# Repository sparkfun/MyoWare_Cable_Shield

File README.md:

MyoWare™ Cable Shield
========================================

[*MyoWare™ Cable Shield (DEV-13687)*](https://www.sparkfun.com/products/13687)

The MyoWare™ Cable Shield is designed to pair with the MyoWare™ Muscle Sensor. This shield provides a jack for a [biomedical sensor pad cable](https://www.sparkfun.com/products/12970).

Repository Contents
-------------------

* **/Hardware** - Eagle design files (.brd, .sch)
* **/Production** - Production panel files (.brd)

Documentation
--------------
* **[Hookup Guide](https://learn.sparkfun.com/tutorials/myoware-muscle-sensor-kit)** - Basic hookup guide for the MyoWare™ Cable Shield.

Product Versions
----------------
* [v1.0](https://www.sparkfun.com/products/13687)- MyoWare™ Cable Shield

License Information
-------------------

This product is _**open source**_!

Please review the LICENSE.md file for license information.

If you have any questions or concerns on licensing, please contact techsupport@sparkfun.com.

Distributed as-is; no warranty is given.

- Your friends at SparkFun.

Designed by Brian E. Kaminski of Advancer Technologies

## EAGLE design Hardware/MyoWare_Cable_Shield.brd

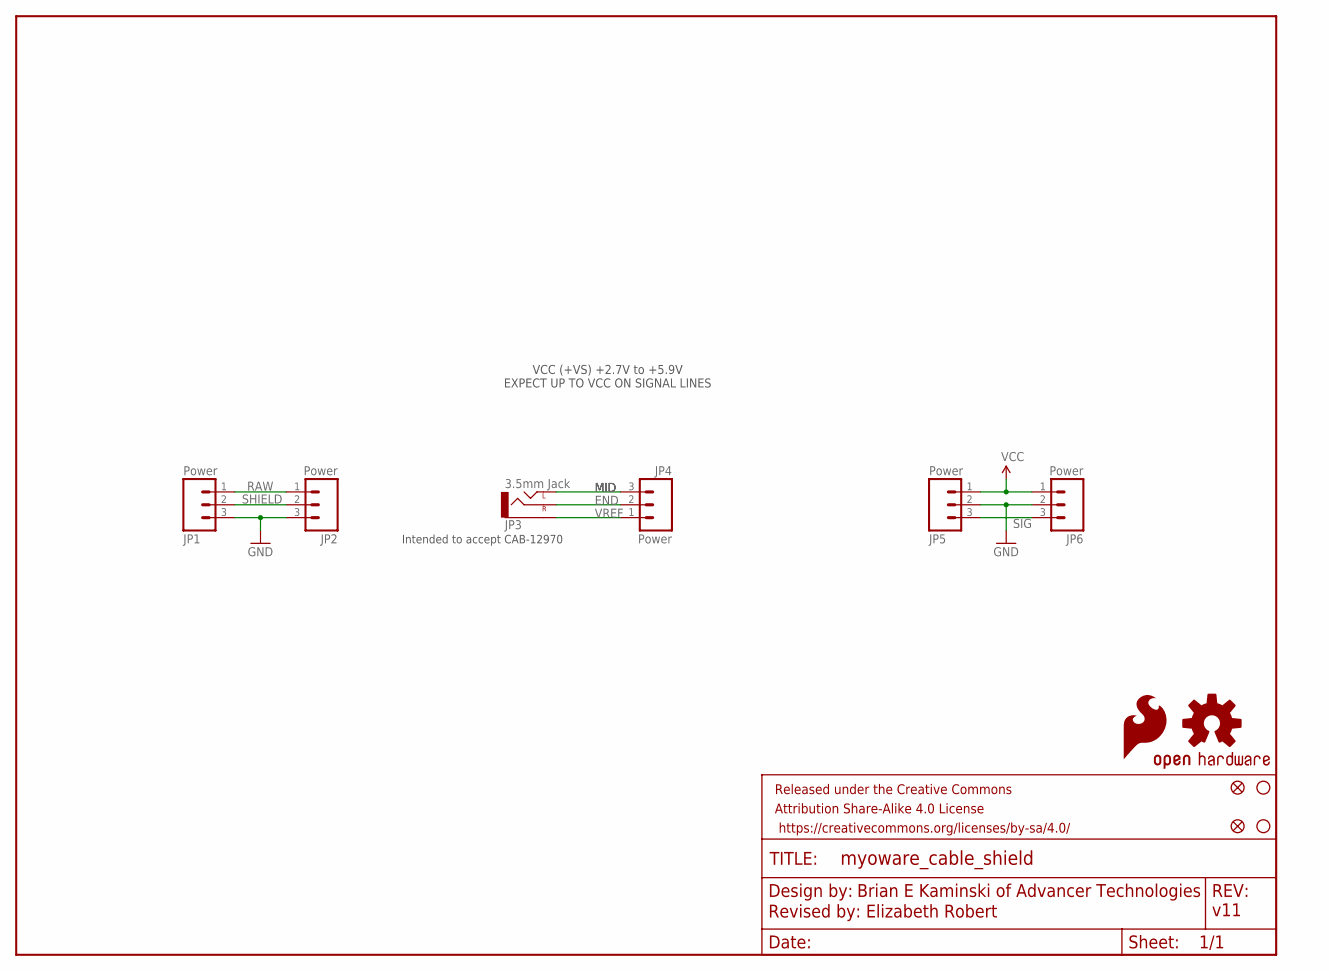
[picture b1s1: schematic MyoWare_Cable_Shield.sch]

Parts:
FID1, FID2: FIDUCIAL1X2; FIDUCIAL-1X2
FRAME1: FRAME-LETTER; CREATIVE_COMMONS
JP1, JP2, JP4, JP5, JP6: Power; 1X03_NO_SILK
JP3: 3.5mm Jack; AUDIO-JACK-3.5MM-SMD
LOGO1: SFE_LOGO_FLAME.2_INCH; SFE_LOGO_FLAME_.2
LOGO2: OSHW-LOGOM; OSHW-LOGO-M
STANDOFF1, STANDOFF2: STAND-OFF

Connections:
END: JP3.RING (RIGHT), JP4.2
GND: JP1.3, JP2.3, JP5.2, JP6.2
MID: JP3.TIP (LEFT), JP4.3
RAW: JP1.1, JP2.1
SHIELD: JP1.2, JP2.2
SIG: JP5.3, JP6.3
VCC: JP5.1, JP6.1
VREF: JP3.SLEEVE, JP4.1

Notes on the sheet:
Brian E Kaminski of Advancer Technologies
Revised by: Elizabeth Robert
v11
VCC (+VS) +2.7V to +5.9V EXPECT UP TO VCC ON SIGNAL LINES
Intended to accept CAB-12970

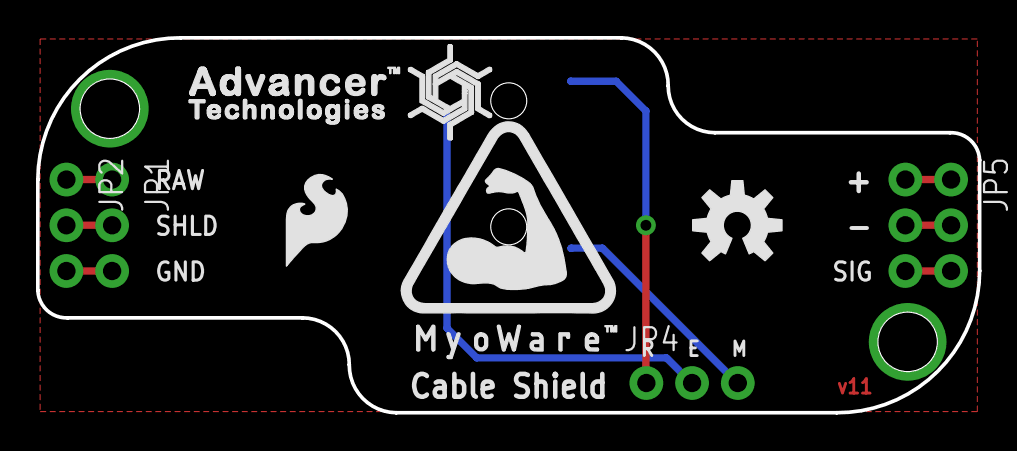
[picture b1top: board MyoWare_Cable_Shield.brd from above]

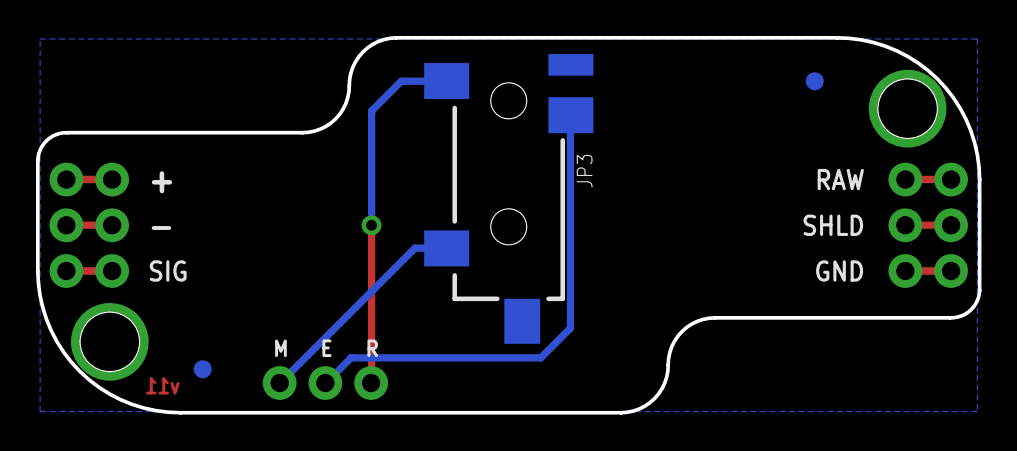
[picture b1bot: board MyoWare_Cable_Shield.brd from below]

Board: 2 copper layers, 52.3 x 20.8 mm, 13 parts (3 on the bottom side), 8 nets.

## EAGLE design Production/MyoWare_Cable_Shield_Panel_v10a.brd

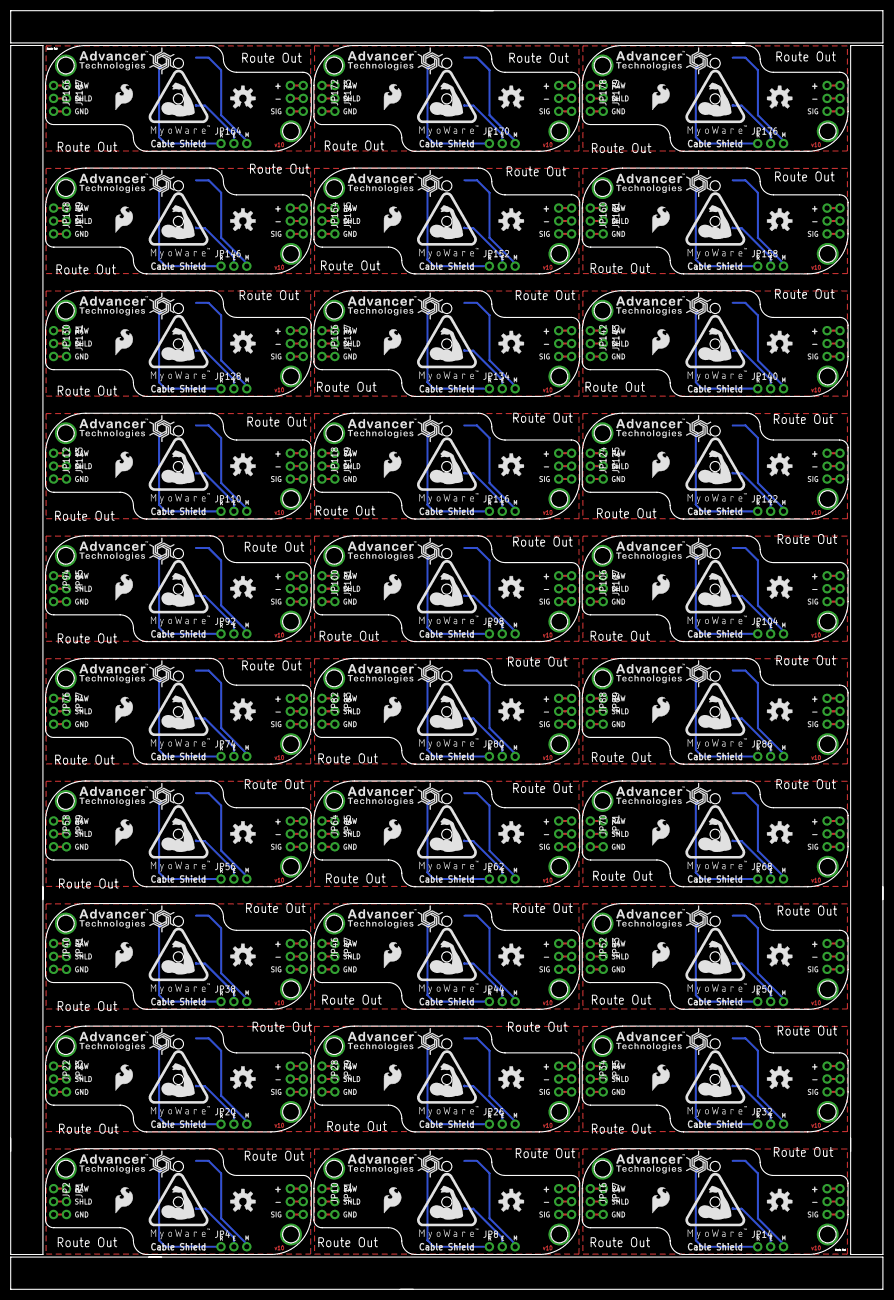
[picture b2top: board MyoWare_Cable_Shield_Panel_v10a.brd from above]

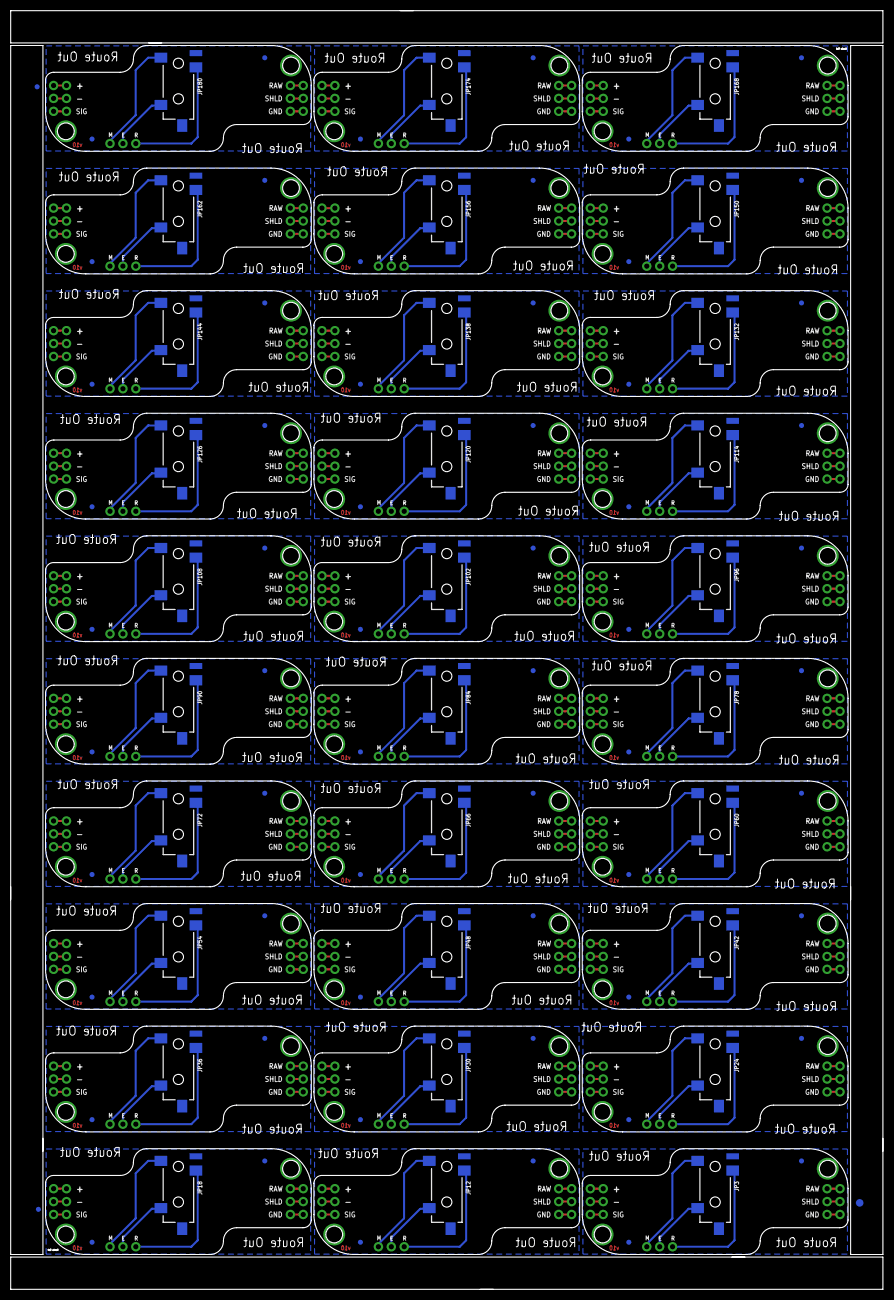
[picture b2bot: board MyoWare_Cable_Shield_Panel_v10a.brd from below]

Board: 2 copper layers, 171.7 x 251.7 mm, 453 parts (93 on the bottom side), 240 nets.

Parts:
E$1: FIDUCIAL-1.5X3
E$5, E$6: FIDUCIAL-1X2
FID1, FID2, FID3, FID4, FID5, FID6, FID7, FID8, FID9, FID10, FID11, FID12, FID13, FID14, FID15, FID16, FID17, FID18, FID19, FID20, FID21, FID22, FID23, FID24, FID25, FID26, FID27, FID28, FID29, FID30, FID31, FID32, FID33, FID34, FID35, FID36, FID37, FID38, FID39, FID40, FID41, FID42, FID43, FID44, FID45, FID46, FID47, FID48, FID49, FID50, FID51, FID52, FID53, FID54, FID55, FID56, FID57, FID58, FID59, FID60: FIDUCIAL1X2; FIDUCIAL-1X2
JP1, JP2, JP4, JP5, JP6, JP7, JP8, JP9, JP10, JP11, JP13, JP14, JP15, JP16, JP17, JP19, JP20, JP21, JP22, JP23, JP25, JP26, JP27, JP28, JP29, JP31, JP32, JP33, JP34, JP35, JP37, JP38, JP39, JP40, JP41, JP43, JP44, JP45, JP46, JP47, JP49, JP50, JP51, JP52, JP53, JP55, JP56, JP57, JP58, JP59, JP61, JP62, JP63, JP64, JP65, JP67, JP68, JP69, JP70, JP71, JP73, JP74, JP75, JP76, JP77, JP79, JP80, JP81, JP82, JP83, JP85, JP86, JP87, JP88, JP89, JP91, JP92, JP93, JP94, JP95, JP97, JP98, JP99, JP100, JP101, JP103, JP104, JP105, JP106, JP107, JP109, JP110, JP111, JP112, JP113, JP115, JP116, JP117, JP118, JP119, JP121, JP122, JP123, JP124, JP125, JP127, JP128, JP129, JP130, JP131, JP133, JP134, JP135, JP136, JP137, JP139, JP140, JP141, JP142, JP143, JP145, JP146, JP147, JP148, JP149, JP151, JP152, JP153, JP154, JP155, JP157, JP158, JP159, JP160, JP161, JP163, JP164, JP165, JP166, JP167, JP169, JP170, JP171, JP172, JP173, JP175, JP176, JP177, JP178, JP179: Power; 1X03_NO_SILK
JP3, JP12, JP18, JP24, JP30, JP36, JP42, JP48, JP54, JP60, JP66, JP72, JP78, JP84, JP90, JP96, JP102, JP108, JP114, JP120, JP126, JP132, JP138, JP144, JP150, JP156, JP162, JP168, JP174, JP180: 3.5mm Jack; AUDIO-JACK-3.5MM-SMD
LOGO, LOGO3, LOGO6, LOGO9, LOGO12, LOGO15, LOGO18, LOGO21, LOGO24, LOGO27, LOGO30, LOGO33, LOGO36, LOGO39, LOGO42, LOGO45, LOGO48, LOGO51, LOGO54, LOGO57, LOGO60, LOGO63, LOGO66, LOGO69, LOGO72, LOGO75, LOGO78, LOGO81, LOGO84, LOGO87: MYOWARE_LOGO
LOGO1, LOGO5, LOGO8, LOGO11, LOGO14, LOGO17, LOGO20, LOGO23, LOGO26, LOGO29, LOGO32, LOGO35, LOGO38, LOGO41, LOGO44, LOGO47, LOGO50, LOGO53, LOGO56, LOGO59, LOGO62, LOGO65, LOGO68, LOGO71, LOGO74, LOGO77, LOGO80, LOGO83, LOGO86, LOGO89: SFE_LOGO_FLAME.2_INCH; SFE_LOGO_FLAME_.2
LOGO2, LOGO4, LOGO7, LOGO10, LOGO13, LOGO16, LOGO19, LOGO22, LOGO25, LOGO28, LOGO31, LOGO34, LOGO37, LOGO40, LOGO43, LOGO46, LOGO49, LOGO52, LOGO55, LOGO58, LOGO61, LOGO64, LOGO67, LOGO70, LOGO73, LOGO76, LOGO79, LOGO82, LOGO85, LOGO88: OSHW-LOGOM; OSHW-LOGO-M
SPIRAL, SPIRAL1, SPIRAL2, SPIRAL3, SPIRAL4, SPIRAL5, SPIRAL6, SPIRAL7, SPIRAL8, SPIRAL9, SPIRAL10, SPIRAL11, SPIRAL12, SPIRAL13, SPIRAL14, SPIRAL15, SPIRAL16, SPIRAL17, SPIRAL18, SPIRAL19, SPIRAL20, SPIRAL21, SPIRAL22, SPIRAL23, SPIRAL24, SPIRAL25, SPIRAL26, SPIRAL27, SPIRAL28, SPIRAL29: SPIRAL_LOGO_60%
STANDOFF1, STANDOFF2, STANDOFF3, STANDOFF4, STANDOFF5, STANDOFF6, STANDOFF7, STANDOFF8, STANDOFF9, STANDOFF10, STANDOFF11, STANDOFF12, STANDOFF13, STANDOFF14, STANDOFF15, STANDOFF16, STANDOFF17, STANDOFF18, STANDOFF19, STANDOFF20, STANDOFF21, STANDOFF22, STANDOFF23, STANDOFF24, STANDOFF25, STANDOFF26, STANDOFF27, STANDOFF28, STANDOFF29, STANDOFF30, STANDOFF31, STANDOFF32, STANDOFF33, STANDOFF34, STANDOFF35, STANDOFF36, STANDOFF37, STANDOFF38, STANDOFF39, STANDOFF40, STANDOFF41, STANDOFF42, STANDOFF43, STANDOFF44, STANDOFF45, STANDOFF46, STANDOFF47, STANDOFF48, STANDOFF49, STANDOFF50, STANDOFF51, STANDOFF52, STANDOFF53, STANDOFF54, STANDOFF55, STANDOFF56, STANDOFF57, STANDOFF58, STANDOFF59, STANDOFF60: STAND-OFF
U$1, U$2, U$3, U$4, U$5, U$6, U$7, U$8, U$9, U$10, U$11, U$12, U$13, U$14, U$15, U$16, U$17, U$18, U$19, U$20, U$21, U$22, U$23, U$24, U$25, U$26, U$27, U$28, U$29, U$30: ADVANCER_LOGO

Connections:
END: JP3.TIP, JP4.2
END1: JP8.2, JP12.TIP
END2: JP14.2, JP18.TIP
END3: JP20.2, JP24.TIP
END4: JP26.2, JP30.TIP
END5: JP32.2, JP36.TIP
END6: JP38.2, JP42.TIP
END7: JP44.2, JP48.TIP
END8: JP50.2, JP54.TIP
END9: JP56.2, JP60.TIP
END10: JP62.2, JP66.TIP
END11: JP68.2, JP72.TIP
END12: JP74.2, JP78.TIP
END13: JP80.2, JP84.TIP
END14: JP86.2, JP90.TIP
END15: JP92.2, JP96.TIP
END16: JP98.2, JP102.TIP
END17: JP104.2, JP108.TIP
END18: JP110.2, JP114.TIP
END19: JP116.2, JP120.TIP
END20: JP122.2, JP126.TIP
END21: JP128.2, JP132.TIP
END22: JP134.2, JP138.TIP
END23: JP140.2, JP144.TIP
END24: JP146.2, JP150.TIP
END25: JP152.2, JP156.TIP
END26: JP158.2, JP162.TIP
END27: JP164.2, JP168.TIP
END28: JP170.2, JP174.TIP
END29: JP176.2, JP180.TIP
GND: JP1.3, JP2.3, JP5.2, JP6.2
GND1: JP7.2, JP9.2, JP10.3, JP11.3
GND2: JP13.2, JP15.2, JP16.3, JP17.3
GND3: JP19.2, JP21.2, JP22.3, JP23.3
GND4: JP25.2, JP27.2, JP28.3, JP29.3
GND5: JP31.2, JP33.2, JP34.3, JP35.3
GND6: JP37.2, JP39.2, JP40.3, JP41.3
GND7: JP43.2, JP45.2, JP46.3, JP47.3
GND8: JP49.2, JP51.2, JP52.3, JP53.3
GND9: JP55.2, JP57.2, JP58.3, JP59.3
GND10: JP61.2, JP63.2, JP64.3, JP65.3
GND11: JP67.2, JP69.2, JP70.3, JP71.3
GND12: JP73.2, JP75.2, JP76.3, JP77.3
GND13: JP79.2, JP81.2, JP82.3, JP83.3
GND14: JP85.2, JP87.2, JP88.3, JP89.3
GND15: JP91.2, JP93.2, JP94.3, JP95.3
GND16: JP97.2, JP99.2, JP100.3, JP101.3
GND17: JP103.2, JP105.2, JP106.3, JP107.3
GND18: JP109.2, JP111.2, JP112.3, JP113.3
GND19: JP115.2, JP117.2, JP118.3, JP119.3
GND20: JP121.2, JP123.2, JP124.3, JP125.3
GND21: JP127.2, JP129.2, JP130.3, JP131.3
GND22: JP133.2, JP135.2, JP136.3, JP137.3
GND23: JP139.2, JP141.2, JP142.3, JP143.3
GND24: JP145.2, JP147.2, JP148.3, JP149.3
GND25: JP151.2, JP153.2, JP154.3, JP155.3
GND26: JP157.2, JP159.2, JP160.3, JP161.3
GND27: JP163.2, JP165.2, JP166.3, JP167.3
GND28: JP169.2, JP171.2, JP172.3, JP173.3
GND29: JP175.2, JP177.2, JP178.3, JP179.3
MID: JP3.SLEEVE, JP4.3
MID1: JP8.3, JP12.SLEEVE
MID2: JP14.3, JP18.SLEEVE
MID3: JP20.3, JP24.SLEEVE
MID4: JP26.3, JP30.SLEEVE
MID5: JP32.3, JP36.SLEEVE
MID6: JP38.3, JP42.SLEEVE
MID7: JP44.3, JP48.SLEEVE
MID8: JP50.3, JP54.SLEEVE
MID9: JP56.3, JP60.SLEEVE
MID10: JP62.3, JP66.SLEEVE
MID11: JP68.3, JP72.SLEEVE
MID12: JP74.3, JP78.SLEEVE
MID13: JP80.3, JP84.SLEEVE
MID14: JP86.3, JP90.SLEEVE
MID15: JP92.3, JP96.SLEEVE
MID16: JP98.3, JP102.SLEEVE
MID17: JP104.3, JP108.SLEEVE
MID18: JP110.3, JP114.SLEEVE
MID19: JP116.3, JP120.SLEEVE
MID20: JP122.3, JP126.SLEEVE
MID21: JP128.3, JP132.SLEEVE
MID22: JP134.3, JP138.SLEEVE
MID23: JP140.3, JP144.SLEEVE
MID24: JP146.3, JP150.SLEEVE
MID25: JP152.3, JP156.SLEEVE
MID26: JP158.3, JP162.SLEEVE
MID27: JP164.3, JP168.SLEEVE
MID28: JP170.3, JP174.SLEEVE
MID29: JP176.3, JP180.SLEEVE
RAW: JP1.1, JP2.1
RAW1: JP10.1, JP11.1
RAW2: JP16.1, JP17.1
RAW3: JP22.1, JP23.1
RAW4: JP28.1, JP29.1
RAW5: JP34.1, JP35.1
RAW6: JP40.1, JP41.1
RAW7: JP46.1, JP47.1
RAW8: JP52.1, JP53.1
RAW9: JP58.1, JP59.1
RAW10: JP64.1, JP65.1
RAW11: JP70.1, JP71.1
RAW12: JP76.1, JP77.1
RAW13: JP82.1, JP83.1
RAW14: JP88.1, JP89.1
RAW15: JP94.1, JP95.1
RAW16: JP100.1, JP101.1
RAW17: JP106.1, JP107.1
RAW18: JP112.1, JP113.1
RAW19: JP118.1, JP119.1
RAW20: JP124.1, JP125.1
RAW21: JP130.1, JP131.1
RAW22: JP136.1, JP137.1
RAW23: JP142.1, JP143.1
RAW24: JP148.1, JP149.1
RAW25: JP154.1, JP155.1
RAW26: JP160.1, JP161.1
RAW27: JP166.1, JP167.1
RAW28: JP172.1, JP173.1
RAW29: JP178.1, JP179.1
SHIELD: JP1.2, JP2.2
SHIELD1: JP10.2, JP11.2
SHIELD2: JP16.2, JP17.2
SHIELD3: JP22.2, JP23.2
SHIELD4: JP28.2, JP29.2
SHIELD5: JP34.2, JP35.2
SHIELD6: JP40.2, JP41.2
SHIELD7: JP46.2, JP47.2
SHIELD8: JP52.2, JP53.2
SHIELD9: JP58.2, JP59.2
SHIELD10: JP64.2, JP65.2
SHIELD11: JP70.2, JP71.2
SHIELD12: JP76.2, JP77.2
SHIELD13: JP82.2, JP83.2
SHIELD14: JP88.2, JP89.2
SHIELD15: JP94.2, JP95.2
SHIELD16: JP100.2, JP101.2
SHIELD17: JP106.2, JP107.2
SHIELD18: JP112.2, JP113.2
SHIELD19: JP118.2, JP119.2
SHIELD20: JP124.2, JP125.2
SHIELD21: JP130.2, JP131.2
SHIELD22: JP136.2, JP137.2
SHIELD23: JP142.2, JP143.2
SHIELD24: JP148.2, JP149.2
SHIELD25: JP154.2, JP155.2
SHIELD26: JP160.2, JP161.2
SHIELD27: JP166.2, JP167.2
SHIELD28: JP172.2, JP173.2
SHIELD29: JP178.2, JP179.2
SIG: JP5.3, JP6.3
SIG1: JP7.3, JP9.3
SIG2: JP13.3, JP15.3
SIG3: JP19.3, JP21.3
SIG4: JP25.3, JP27.3
SIG5: JP31.3, JP33.3
SIG6: JP37.3, JP39.3
SIG7: JP43.3, JP45.3
SIG8: JP49.3, JP51.3
SIG9: JP55.3, JP57.3
SIG10: JP61.3, JP63.3
SIG11: JP67.3, JP69.3
SIG12: JP73.3, JP75.3
SIG13: JP79.3, JP81.3
SIG14: JP85.3, JP87.3
SIG15: JP91.3, JP93.3
SIG16: JP97.3, JP99.3
SIG17: JP103.3, JP105.3
SIG18: JP109.3, JP111.3
SIG19: JP115.3, JP117.3
SIG20: JP121.3, JP123.3
SIG21: JP127.3, JP129.3
SIG22: JP133.3, JP135.3
SIG23: JP139.3, JP141.3
SIG24: JP145.3, JP147.3
SIG25: JP151.3, JP153.3
SIG26: JP157.3, JP159.3
SIG27: JP163.3, JP165.3
SIG28: JP169.3, JP171.3
SIG29: JP175.3, JP177.3
VCC: JP5.1, JP6.1
VCC1: JP7.1, JP9.1
VCC2: JP13.1, JP15.1
VCC3: JP19.1, JP21.1
VCC4: JP25.1, JP27.1
VCC5: JP31.1, JP33.1
VCC6: JP37.1, JP39.1
VCC7: JP43.1, JP45.1
VCC8: JP49.1, JP51.1
VCC9: JP55.1, JP57.1
VCC10: JP61.1, JP63.1
VCC11: JP67.1, JP69.1
VCC12: JP73.1, JP75.1
VCC13: JP79.1, JP81.1
VCC14: JP85.1, JP87.1
VCC15: JP91.1, JP93.1
VCC16: JP97.1, JP99.1
VCC17: JP103.1, JP105.1
VCC18: JP109.1, JP111.1
VCC19: JP115.1, JP117.1
VCC20: JP121.1, JP123.1
VCC21: JP127.1, JP129.1
VCC22: JP133.1, JP135.1
VCC23: JP139.1, JP141.1
VCC24: JP145.1, JP147.1
VCC25: JP151.1, JP153.1
VCC26: JP157.1, JP159.1
VCC27: JP163.1, JP165.1
VCC28: JP169.1, JP171.1
VCC29: JP175.1, JP177.1
VREF: JP3.RING, JP4.1
VREF1: JP8.1, JP12.RING
VREF2: JP14.1, JP18.RING
VREF3: JP20.1, JP24.RING
VREF4: JP26.1, JP30.RING
VREF5: JP32.1, JP36.RING
VREF6: JP38.1, JP42.RING
VREF7: JP44.1, JP48.RING
VREF8: JP50.1, JP54.RING
VREF9: JP56.1, JP60.RING
VREF10: JP62.1, JP66.RING
VREF11: JP68.1, JP72.RING
VREF12: JP74.1, JP78.RING
VREF13: JP80.1, JP84.RING
VREF14: JP86.1, JP90.RING
VREF15: JP92.1, JP96.RING
VREF16: JP98.1, JP102.RING
VREF17: JP104.1, JP108.RING
VREF18: JP110.1, JP114.RING
VREF19: JP116.1, JP120.RING
VREF20: JP122.1, JP126.RING
VREF21: JP128.1, JP132.RING
VREF22: JP134.1, JP138.RING
VREF23: JP140.1, JP144.RING
VREF24: JP146.1, JP150.RING
VREF25: JP152.1, JP156.RING
VREF26: JP158.1, JP162.RING
VREF27: JP164.1, JP168.RING
VREF28: JP170.1, JP174.RING
VREF29: JP176.1, JP180.RING

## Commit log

2015-07-14 changed audio jack to our common part
2015-09-09 Added cam friendlier versions of the RoSH and PB Free images
2015-09-09 Bumped version number to 10 on sch
2015-09-09 Gave the jack a value of '3.5mm jack'
2015-09-11 scooted the fiducials inward just a bit for better recognition
2015-09-14 Cleaned up dimension symmetry & started a panel
2015-09-16 removing old panel and test panel
2015-09-16 deleting panel
2015-09-16 scooted dimension lines to 0.01 inch grid
2015-09-17 created panel v10
2015-09-21 Removed RoHS claim
2015-09-22 Approved DRC errors
2015-09-22 Updated measures layer
2015-10-14 v10a panel gerbers
    ROHS removed
2016-03-14 Changed some dimension units to inches
2016-12-12 V11
    REM Headers Lining Up
    Traces Adjusted
    Board Origin Fix
2016-12-12 V11 Small Change to REM Position
2016-12-14 Minor Adjustment
2016-12-15 Final Adjust before Protos
2017-01-16 Replaced bitmap logos with vector logos
2017-01-19 Rewiring of 3.5mm Jack
2017-01-19 Design Review Changes
    Via to top board change to round instead of square
    Dimensions on board fixed
2017-01-19 DRC Change
2017-01-19 DRC Changes
2017-02-21 .BRD Layer
2017-02-21 Revert "V11"
2017-02-21 Drill Legend Addition
2017-05-09 Schematic Change
    3.5 mm jack footprint orientation

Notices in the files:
parts and their libraries:
SparkFun-Connectors: Licensing: CC v3.0 Share-Alike You are welcome to use this library for commercial purposes.
SparkFun-Aesthetics: Licensing: Creative Commons ShareAlike 4.0 International - https://creativecommons.org/licenses/by-sa/4.0
SparkFun-Aesthetics: Released under the Creative Commons
